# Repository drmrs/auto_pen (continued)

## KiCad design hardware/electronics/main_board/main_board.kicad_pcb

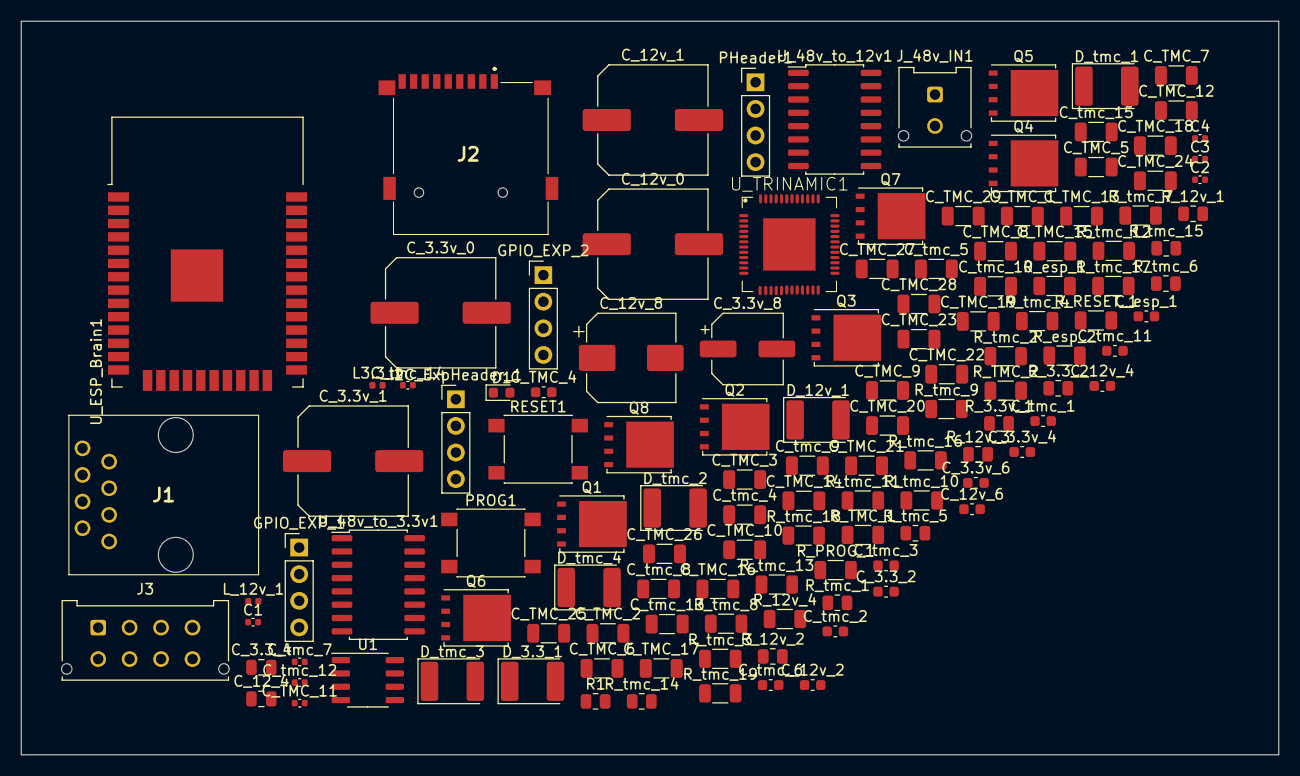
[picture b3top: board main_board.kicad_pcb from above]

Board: 2 copper layers, 120.0 x 70.0 mm, 127 parts (0 on the bottom side), 88 nets, no tracks yet.

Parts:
C1, C3: 10uF; C_0402_1005Metric
C2, C4: 100nF; C_0402_1005Metric
C_3.3_2, C_12v_2: 2.7nF; C_0603_1608Metric
C_3.3_4, C_12_4: 22nF; C_0805_2012Metric
C_3.3v_0, C_3.3v_1, C_12v_0, C_12v_1: 220uF; C_Elec_10x10.2
C_3.3v_4, C_3.3v_6, C_12v_4, C_12v_6: 100nF; C_0603_1608Metric
C_3.3v_8: 330uF; CP_Elec_6.3x5.9
C_12v_8: 330uF; CP_Elec_8x10
C_TMC_1, C_TMC_2, C_TMC_3, C_TMC_5, C_TMC_6, C_TMC_7, C_TMC_8, C_TMC_9, C_TMC_10, C_TMC_12, C_TMC_13, C_TMC_15, C_TMC_16, C_TMC_17, C_TMC_18, C_TMC_19, C_TMC_20, C_TMC_21, C_TMC_22, C_TMC_23, C_TMC_24, C_TMC_25, C_TMC_26, C_TMC_27, C_TMC_28, C_TMC_29: 1n; C_1206_3216Metric
C_TMC_4: 100nF; C_0603_1608Metric
C_TMC_11: 100n; C_0402_1005Metric
C_TMC_14: 100nF; C_1206_3216Metric
C_esp_1: 470n; C_0603_1608Metric
C_tmc_1, C_tmc_2, C_tmc_6, C_tmc_11: 2.2u; C_0603_1608Metric
C_tmc_3: 470n; C_0603_1608Metric
C_tmc_4, C_tmc_5, C_tmc_9, C_tmc_10: 220nF; C_1206_3216Metric
C_tmc_7, C_tmc_12, C_tmc_14: 100nF; C_0402_1005Metric
C_tmc_8: 470nF; C_1206_3216Metric
C_tmc_13, C_tmc_15: 4.7uF; C_1206_3216Metric
D1: LED; LED_0603_1608Metric
D_3.3_1, D_12v_1: STPS3L60U; D_2114_3652Metric
D_tmc_1, D_tmc_2, D_tmc_3, D_tmc_4: STPS3L60U; D_2114_3652Metric
GPIO_EXP_1, GPIO_EXP_2: Conn_01x04_Male; PinHeader_1x04_P2.54mm_Vertical
I2C_ExpHeader_1: Conn_01x04_Male; PinHeader_1x04_P2.54mm_Vertical
J1: 215877-1; 2158771
J2: TF-15X15; TF15X15
J3: Conn_02x04_Odd_Even; Molex_Micro-Fit_3.0_43045-0812_2x04_P3.00mm_Vertical
J_48v_IN1: Molex; Molex_Micro-Fit_3.0_43045-0212_2x01_P3.00mm_Vertical
L3.3_1: 126uH; L_0402_1005Metric
L_12v_1: 126uH; L_0402_1005Metric
PHeader1: Conn_01x04_Male; PinHeader_1x04_P2.54mm_Vertical
PROG1: SW_Push_Dual_x2; SW_Push_1P1T_NO_6x6mm_H9.5mm
Q1, Q2, Q3, Q4, Q5, Q6, Q7, Q8: CSD18537NQ5A; TDSON-8-1
R1: 300 Ohms; R_0805_2012Metric
RESET1: SW_Push_Dual_x2; SW_Push_1P1T_NO_6x6mm_H9.5mm
R_3.3_2, R_12v_2: 9.1kohms; R_0805_2012Metric
R_3.3v_1, R_12v_1: 20Kohms; R_0805_2012Metric
R_12v_3: 12kOhms; R_0805_2012Metric
R_12v_4: 4.7KOhms; R_1206_3216Metric
R_PROG_1: 10kOhms; R_1206_3216Metric
R_RESET_1: 10kOhms; R_1206_3216Metric
R_TMC_1, R_TMC_2: 10kOhms; R_1206_3216Metric
R_esp_1, R_esp_2: 4.7KOhms; R_1206_3216Metric
R_tmc_1: 2R2; R_0805_2012Metric
R_tmc_2, R_tmc_3, R_tmc_4, R_tmc_7, R_tmc_8, R_tmc_9, R_tmc_10, R_tmc_11, R_tmc_12, R_tmc_13, R_tmc_16, R_tmc_17, R_tmc_18, R_tmc_19: 10Ohm; R_1206_3216Metric
R_tmc_5, R_tmc_6, R_tmc_14, R_tmc_15: 47R; R_0805_2012Metric
U1: P82B96; SO-8_3.9x4.9mm_P1.27mm
U_48v_to_3.3v1, U_48v_to_12v1: L4978D; SO-16_5.3x10.2mm_P1.27mm
U_ESP_Brain1: ESP32-WROOM-32
U_TRINAMIC1: TMC5160-TA; eTQFP48

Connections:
3.3v_Program: C1.1, C1.2, C2.1, C2.2, C3.1, C3.2, C4.1, C4.2, C_3.3_2.2, C_3.3_4.2, C_3.3v_0.2, C_3.3v_1.2, C_3.3v_4.2, C_3.3v_8.1, C_3.3v_8.2, C_12_4.2, C_12v_0.2, C_12v_1.2, C_12v_2.2, C_12v_4.2, C_12v_8.2, C_TMC_4.1, C_TMC_4.2, C_TMC_14.2, C_TMC_26.1, C_TMC_27.1, C_TMC_28.1, C_TMC_29.1, C_esp_1.2, C_tmc_1.2, C_tmc_2.1, C_tmc_3.1, C_tmc_7.2, C_tmc_8.2, C_tmc_12.2, C_tmc_13.2, C_tmc_14.2, C_tmc_15.2, D_3.3_1.2, D_12v_1.2, D_tmc_1.2, D_tmc_2.2, D_tmc_3.2, D_tmc_4.2, J1.2, J1.6, J2.4, J2.6, J2.MP1, J_48v_IN1.1, L3.3_1.2, PHeader1.1, PHeader1.4, PROG1.1, R1.1, RESET1.1, R_12v_4.2, R_PROG_1.1, R_RESET_1.1, R_TMC_1.1, R_TMC_2.1, R_esp_1.1, R_esp_2.2, R_tmc_6.2, R_tmc_8.2, R_tmc_15.2, R_tmc_17.2, U1.4, U_48v_to_3.3v1.2, U_48v_to_3.3v1.14, U_48v_to_12v1.2, U_ESP_Brain1.1, U_ESP_Brain1.2, U_ESP_Brain1.15, U_ESP_Brain1.38, U_ESP_Brain1.39, U_TRINAMIC1.6, U_TRINAMIC1.11, U_TRINAMIC1.12, U_TRINAMIC1.19, U_TRINAMIC1.20, U_TRINAMIC1.22, U_TRINAMIC1.30, U_TRINAMIC1.49
ESP_Emergency: J1.4, R_TMC_1.2, U_ESP_Brain1.5, U_TRINAMIC1.28
ESP_GPIO_4: GPIO_EXP_1.1, U_ESP_Brain1.26
ESP_GPIO_16: GPIO_EXP_1.2, U_ESP_Brain1.27
ESP_GPIO_17: GPIO_EXP_1.3, U_ESP_Brain1.28
ESP_GPIO_25: GPIO_EXP_1.4, U_ESP_Brain1.10
ESP_GPIO_26: GPIO_EXP_2.1, U_ESP_Brain1.11
ESP_GPIO_27: GPIO_EXP_2.2, U_ESP_Brain1.12
ESP_GPIO_32: GPIO_EXP_2.3, U_ESP_Brain1.8
ESP_GPIO_33: GPIO_EXP_2.4, U_ESP_Brain1.9
ESP_I2C_SCL: I2C_ExpHeader_1.2, I2C_ExpHeader_1.4, R_esp_2.1, U1.7, U_ESP_Brain1.36
ESP_I2C_SDA: I2C_ExpHeader_1.1, I2C_ExpHeader_1.3, R_esp_1.2, U1.1, U_ESP_Brain1.33
ESP_LED: D1.2, U_ESP_Brain1.24
Encoder_A: J3.5, U_TRINAMIC1.24
Encoder_B: J3.6, U_TRINAMIC1.23
Encoder_N: J3.8, U_TRINAMIC1.25
HSPI_CLK: J2.5, U_ESP_Brain1.13
HSPI_CS: J2.2, U_ESP_Brain1.23
HSPI_MISO: J2.7, U_ESP_Brain1.14
HSPI_MOSI: J2.3, U_ESP_Brain1.16
unnamed: C_3.3_2.1, R_3.3v_1.2, U_48v_to_3.3v1.4
unnamed: C_3.3_4.1, R_3.3_2.2
unnamed: C_3.3v_4.1, U_48v_to_3.3v1.3
unnamed: C_3.3v_6.1, D_3.3_1.1, L3.3_1.1, U_48v_to_3.3v1.5
unnamed: C_3.3v_6.2, U_48v_to_3.3v1.12
unnamed: C_12_4.1, R_12v_2.2
unnamed: C_12v_2.1, R_12v_1.2, U_48v_to_12v1.4
unnamed: C_12v_4.1, U_48v_to_12v1.3
unnamed: C_12v_6.1, D_12v_1.1, L_12v_1.1, U_48v_to_12v1.5
unnamed: C_12v_6.2, U_48v_to_12v1.12
unnamed: C_tmc_7.1, Q3.1, Q3.2, Q3.3, Q4.1, Q4.2, Q4.3, R_tmc_5.2, R_tmc_8.1
unnamed: C_tmc_12.1, Q6.1, Q6.2, Q6.3, Q8.1, Q8.2, Q8.3, R_tmc_14.2, R_tmc_17.1
unnamed: D1.1, R1.2
unnamed: J1.1, U1.3
unnamed: J1.3, U1.2
unnamed: J1.5, U1.5
unnamed: J1.7, U1.6
unnamed: Q1.4, R_tmc_10.2
unnamed: Q2.4, R_tmc_2.1
unnamed: Q3.4, R_tmc_3.1
unnamed: Q4.4, R_tmc_9.2
unnamed: Q5.4, R_tmc_11.1
unnamed: Q6.4, R_tmc_12.1
unnamed: Q7.4, R_tmc_19.2
unnamed: Q8.4, R_tmc_18.2
unnamed: R_3.3_2.1, U_48v_to_3.3v1.13
unnamed: R_12v_2.1, U_48v_to_12v1.13
unnamed: R_12v_3.2, R_12v_4.1, U_48v_to_12v1.14
Program: PROG1.2, R_PROG_1.2, U_ESP_Brain1.25
RX_Program: PHeader1.3, U_ESP_Brain1.34
Reset: RESET1.2, R_RESET_1.2, U_ESP_Brain1.3
Stepper_Loop_A_1: C_TMC_26.2, J3.1, Q2.1, Q2.2, Q2.3, Q3.5, R_tmc_4.1
Stepper_Loop_A_2: C_TMC_27.2, J3.2, Q1.1, Q1.2, Q1.3, Q4.5, R_tmc_7.1
Stepper_Loop_B_1: C_TMC_28.2, J3.3, Q5.1, Q5.2, Q5.3, Q6.5, R_tmc_13.1
Stepper_Loop_B_2: C_TMC_29.2, J3.4, Q7.1, Q7.2, Q7.3, Q8.5, R_tmc_16.1
TMC-CP-48v: C_3.3v_0.1, C_3.3v_1.1, C_12v_0.1, C_12v_1.1, C_TMC_11.2, C_TMC_14.1, C_tmc_8.1, C_tmc_13.1, C_tmc_14.1, C_tmc_15.1, J3.7, J_48v_IN1.2, Q1.5, Q2.5, Q5.5, Q7.5, R_3.3v_1.1, R_12v_1.1, U_48v_to_3.3v1.11, U_48v_to_12v1.11, U_TRINAMIC1.33
TMC_5VOUT: C_tmc_2.2, R_tmc_1.1, U_TRINAMIC1.5
TMC_12VOUT: C_12v_8.1, C_esp_1.1, C_tmc_1.1, J1.8, L_12v_1.2, R_12v_3.1, U1.8, U_TRINAMIC1.3, U_TRINAMIC1.4
TMC_BMA1: C_tmc_5.1, D_tmc_1.1, R_tmc_4.2, U_TRINAMIC1.40
TMC_BMA2: C_tmc_4.1, D_tmc_3.1, R_tmc_7.2, U_TRINAMIC1.37
TMC_BMB1: C_tmc_10.1, D_tmc_2.1, R_tmc_13.2, U_TRINAMIC1.48
TMC_BMB2: C_tmc_9.1, D_tmc_4.1, R_tmc_16.2, U_TRINAMIC1.45
TMC_CA1: C_tmc_5.2, U_TRINAMIC1.42
TMC_CA2: C_tmc_4.2, U_TRINAMIC1.35
TMC_CB1: C_tmc_10.2, U_TRINAMIC1.2
TMC_CB2: C_tmc_9.2, U_TRINAMIC1.43
TMC_CPI: C_TMC_1.1, C_TMC_2.1, C_TMC_3.1, C_TMC_5.1, C_TMC_6.1, C_TMC_7.1, C_TMC_8.1, C_TMC_9.1, C_TMC_10.1, C_TMC_12.1, C_TMC_13.1, C_TMC_15.1, C_TMC_16.1, C_TMC_17.1, C_TMC_18.1, C_TMC_19.1, C_TMC_20.1, C_TMC_21.1, C_TMC_22.1, C_TMC_23.1, C_TMC_24.1, C_TMC_25.1, U_TRINAMIC1.32
TMC_CPO: C_TMC_1.2, C_TMC_2.2, C_TMC_3.2, C_TMC_5.2, C_TMC_6.2, C_TMC_7.2, C_TMC_8.2, C_TMC_9.2, C_TMC_10.2, C_TMC_12.2, C_TMC_13.2, C_TMC_15.2, C_TMC_16.2, C_TMC_17.2, C_TMC_18.2, C_TMC_19.2, C_TMC_20.2, C_TMC_21.2, C_TMC_22.2, C_TMC_23.2, C_TMC_24.2, C_TMC_25.2, U_TRINAMIC1.31
TMC_HA1: R_tmc_2.2, U_TRINAMIC1.41
TMC_HA2: R_tmc_10.1, U_TRINAMIC1.36
TMC_HB1: R_tmc_11.2, U_TRINAMIC1.1
TMC_HB2: R_tmc_19.1, U_TRINAMIC1.44
TMC_LA1: R_tmc_3.2, U_TRINAMIC1.39
TMC_LA2: R_tmc_9.1, U_TRINAMIC1.38
TMC_LB1: R_tmc_12.2, U_TRINAMIC1.47
TMC_LB2: R_tmc_18.1, U_TRINAMIC1.46
TMC_Ramp: R_TMC_2.2, U_TRINAMIC1.21
TMC_SRAH: C_tmc_6.1, R_tmc_5.1, U_TRINAMIC1.8
TMC_SRAL: C_tmc_6.2, R_tmc_6.1, U_TRINAMIC1.7
TMC_SRBH: C_tmc_11.1, R_tmc_14.1, U_TRINAMIC1.9
TMC_SRBL: C_tmc_11.2, R_tmc_15.1, U_TRINAMIC1.10
TMC_VCC: C_tmc_3.2, R_tmc_1.2, U_TRINAMIC1.29
TNC_VCP: C_TMC_11.1, U_TRINAMIC1.34
TX_Program: PHeader1.2, U_ESP_Brain1.35
VSPI_CLK: U_ESP_Brain1.30, U_TRINAMIC1.14
VSPI_CS: U_ESP_Brain1.29, U_TRINAMIC1.13
VSPI_MISO: U_ESP_Brain1.31, U_TRINAMIC1.16
VSPI_MOSI: U_ESP_Brain1.37, U_TRINAMIC1.15

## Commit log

2020-04-01 init
2021-02-06 early v2 designs
2021-02-12 added pusher plate for suction cup tools
2021-02-12 fixed so typo
2021-02-12 Typo's, choose pusher plate designs
2021-02-12 Typo's, removed unavailable youtube video url
2021-02-12 fixed some typo's
2021-03-17 added more circut work wip
2021-03-24 pcb looking much better
2021-03-26 case updates
2021-04-02 untested pcb update
2021-04-03 fixed pcb issues - still untested
2021-04-05 updated footprint to generic SOIC-16w so tooling rotates it properly."
2021-07-19 added power split pcb
